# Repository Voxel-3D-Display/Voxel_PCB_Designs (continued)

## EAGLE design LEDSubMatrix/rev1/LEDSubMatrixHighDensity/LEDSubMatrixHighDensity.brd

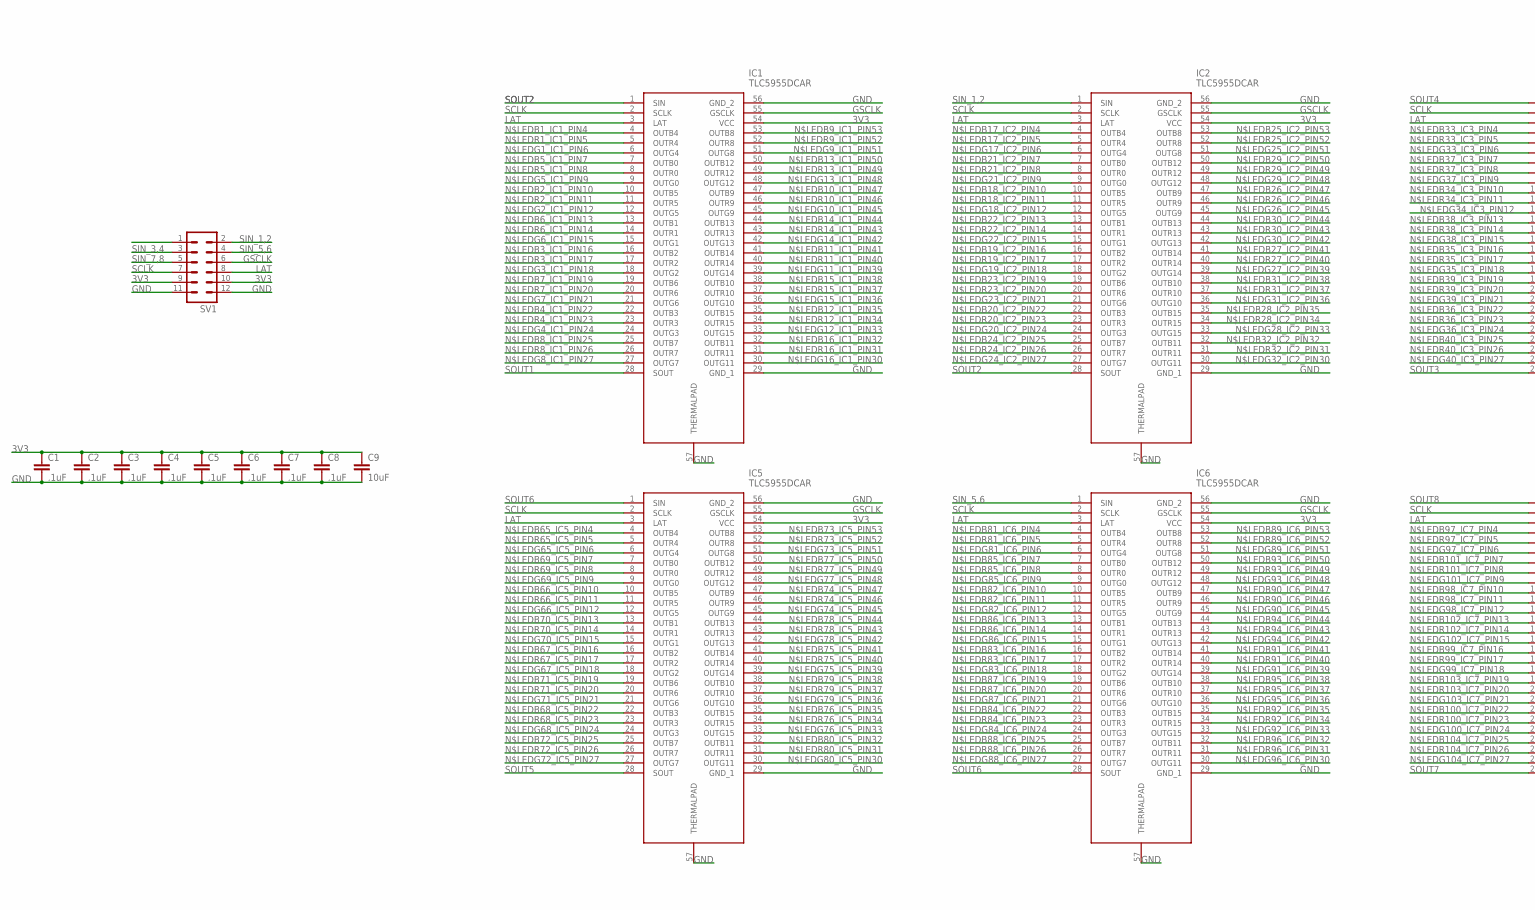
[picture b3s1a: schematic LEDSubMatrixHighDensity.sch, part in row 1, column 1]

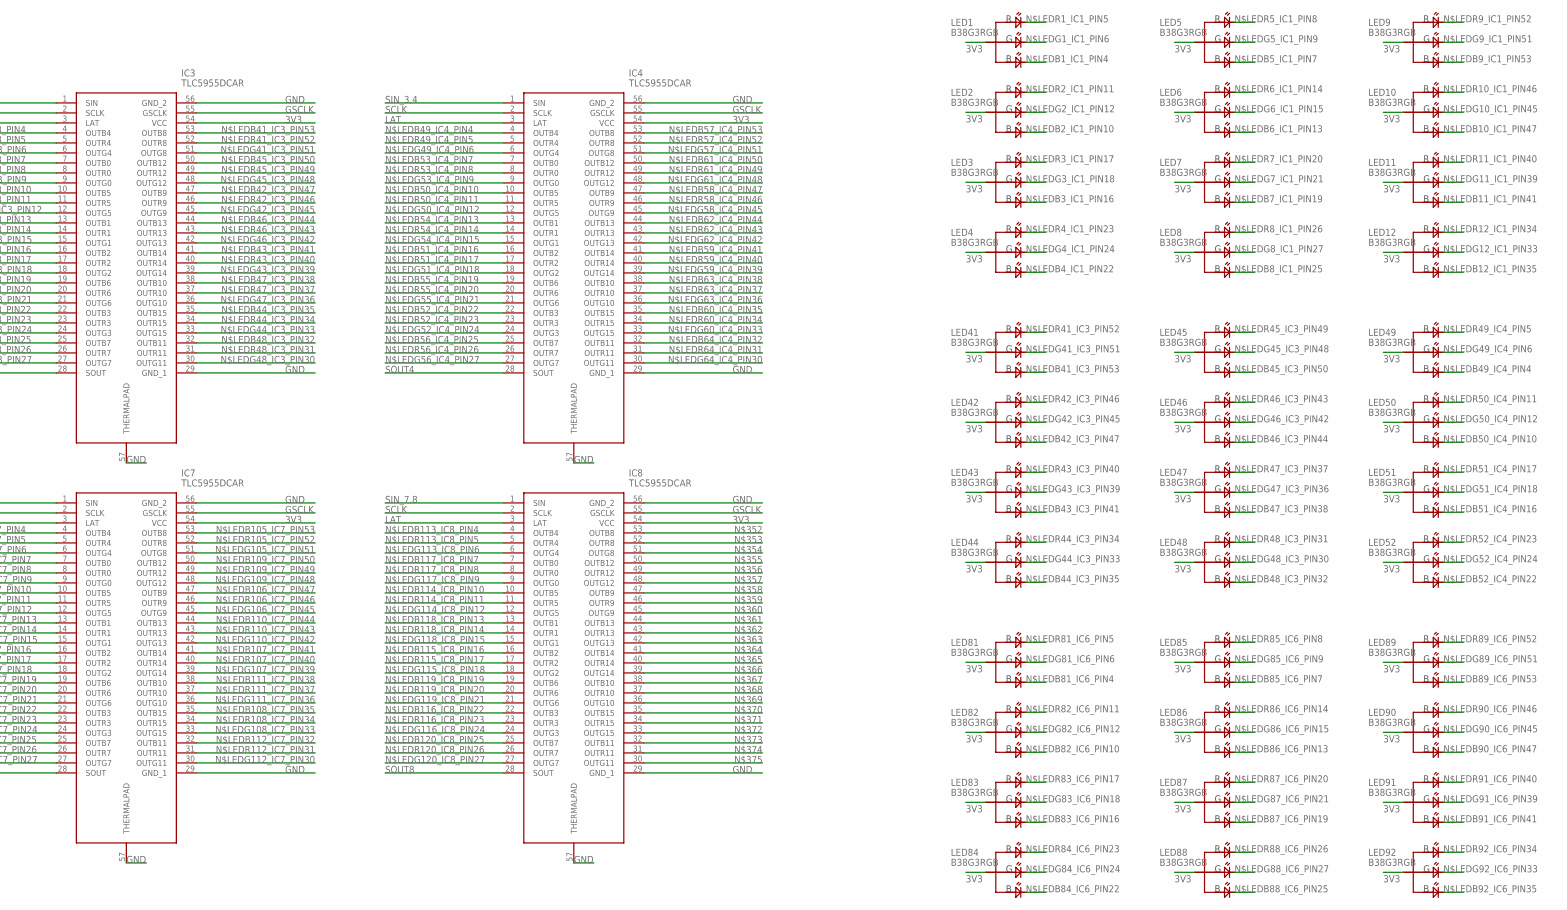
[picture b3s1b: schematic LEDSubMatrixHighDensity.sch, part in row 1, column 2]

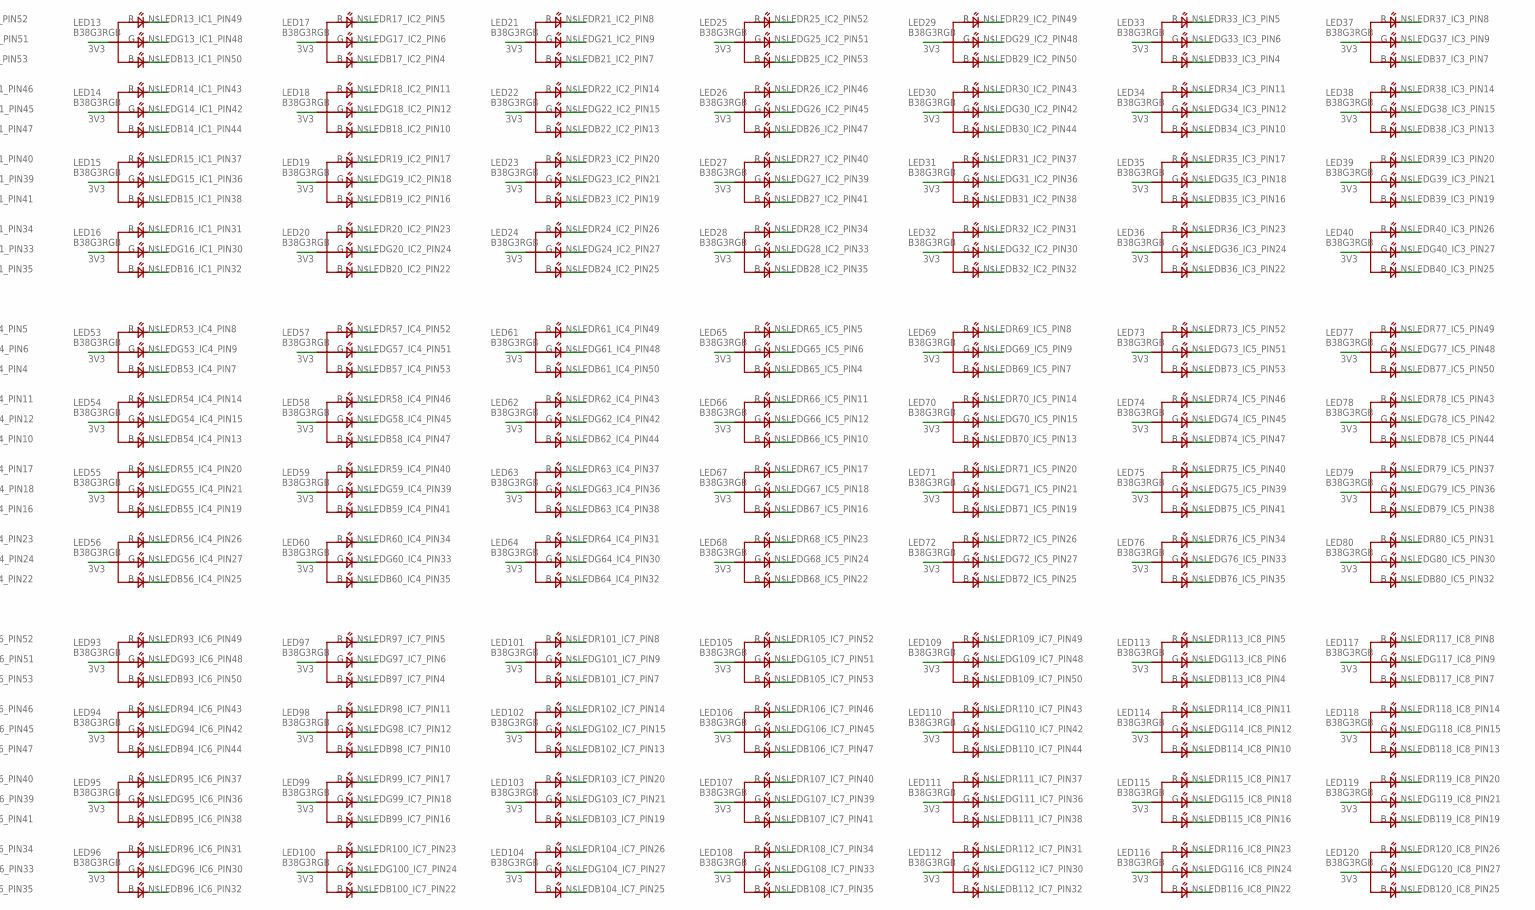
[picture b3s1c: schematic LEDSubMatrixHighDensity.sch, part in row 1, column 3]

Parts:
C1, C2, C3, C4, C5, C6, C7, C8: .1uF; C0603
C9: 10uF; C0805
IC1, IC2, IC3, IC4, IC5, IC6, IC7, IC8: TLC5955DCAR; SOP50P810X120-57N
LED1, LED2, LED3, LED4, LED5, LED6, LED7, LED8, LED9, LED10, LED11, LED12, LED13, LED14, LED15, LED16, LED17, LED18, LED19, LED20, LED21, LED22, LED23, LED24, LED25, LED26, LED27, LED28, LED29, LED30, LED31, LED32, LED33, LED34, LED35, LED36, LED37, LED38, LED39, LED40, LED41, LED42, LED43, LED44, LED45, LED46, LED47, LED48, LED49, LED50, LED51, LED52, LED53, LED54, LED55, LED56, LED57, LED58, LED59, LED60, LED61, LED62, LED63, LED64, LED65, LED66, LED67, LED68, LED69, LED70, LED71, LED72, LED73, LED74, LED75, LED76, LED77, LED78, LED79, LED80, LED81, LED82, LED83, LED84, LED85, LED86, LED87, LED88, LED89, LED90, LED91, LED92, LED93, LED94, LED95, LED96, LED97, LED98, LED99, LED100, LED101, LED102, LED103, LED104, LED105, LED106, LED107, LED108, LED109, LED110, LED111, LED112, LED113, LED114, LED115, LED116, LED117, LED118, LED119, LED120: B38G3RGB
SV1: MA06-2

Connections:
3V3: C1.1, C2.1, C3.1, C4.1, C5.1, C6.1, C7.1, C8.1, C9.1, IC1.54 (VCC), IC2.54 (VCC), IC3.54 (VCC), IC4.54 (VCC), IC5.54 (VCC), IC6.54 (VCC), IC7.54 (VCC), IC8.54 (VCC), LED1.3 (COM), LED2.3 (COM), LED3.3 (COM), LED4.3 (COM), LED5.3 (COM), LED6.3 (COM), LED7.3 (COM), LED8.3 (COM), LED9.3 (COM), LED10.3 (COM), LED11.3 (COM), LED12.3 (COM), LED13.3 (COM), LED14.3 (COM), LED15.3 (COM), LED16.3 (COM), LED17.3 (COM), LED18.3 (COM), LED19.3 (COM), LED20.3 (COM), LED21.3 (COM), LED22.3 (COM), LED23.3 (COM), LED24.3 (COM), LED25.3 (COM), LED26.3 (COM), LED27.3 (COM), LED28.3 (COM), LED29.3 (COM), LED30.3 (COM), LED31.3 (COM), LED32.3 (COM), LED33.3 (COM), LED34.3 (COM), LED35.3 (COM), LED36.3 (COM), LED37.3 (COM), LED38.3 (COM), LED39.3 (COM), LED40.3 (COM), LED41.3 (COM), LED42.3 (COM), LED43.3 (COM), LED44.3 (COM), LED45.3 (COM), LED46.3 (COM), LED47.3 (COM), LED48.3 (COM), LED49.3 (COM), LED50.3 (COM), LED51.3 (COM), LED52.3 (COM), LED53.3 (COM), LED54.3 (COM), LED55.3 (COM), LED56.3 (COM), LED57.3 (COM), LED58.3 (COM), LED59.3 (COM), LED60.3 (COM), LED61.3 (COM), LED62.3 (COM), LED63.3 (COM), LED64.3 (COM), LED65.3 (COM), LED66.3 (COM), LED67.3 (COM), LED68.3 (COM), LED69.3 (COM), LED70.3 (COM), LED71.3 (COM), LED72.3 (COM), LED73.3 (COM), LED74.3 (COM), LED75.3 (COM), LED76.3 (COM), LED77.3 (COM), LED78.3 (COM), LED79.3 (COM), LED80.3 (COM), LED81.3 (COM), LED82.3 (COM), LED83.3 (COM), LED84.3 (COM), LED85.3 (COM), LED86.3 (COM), LED87.3 (COM), LED88.3 (COM), LED89.3 (COM), LED90.3 (COM), LED91.3 (COM), LED92.3 (COM), LED93.3 (COM), LED94.3 (COM), LED95.3 (COM), LED96.3 (COM), LED97.3 (COM), LED98.3 (COM), LED99.3 (COM), LED100.3 (COM), LED101.3 (COM), LED102.3 (COM), LED103.3 (COM), LED104.3 (COM), LED105.3 (COM), LED106.3 (COM), LED107.3 (COM), LED108.3 (COM), LED109.3 (COM), LED110.3 (COM), LED111.3 (COM), LED112.3 (COM), LED113.3 (COM), LED114.3 (COM), LED115.3 (COM), LED116.3 (COM), LED117.3 (COM), LED118.3 (COM), LED119.3 (COM), LED120.3 (COM), SV1.9, SV1.10
GND: C1.2, C2.2, C3.2, C4.2, C5.2, C6.2, C7.2, C8.2, C9.2, IC1.29 (GND_1), IC1.56 (GND_2), IC1.57 (THERMALPAD), IC2.29 (GND_1), IC2.56 (GND_2), IC2.57 (THERMALPAD), IC3.29 (GND_1), IC3.56 (GND_2), IC3.57 (THERMALPAD), IC4.29 (GND_1), IC4.56 (GND_2), IC4.57 (THERMALPAD), IC5.29 (GND_1), IC5.56 (GND_2), IC5.57 (THERMALPAD), IC6.29 (GND_1), IC6.56 (GND_2), IC6.57 (THERMALPAD), IC7.29 (GND_1), IC7.56 (GND_2), IC7.57 (THERMALPAD), IC8.29 (GND_1), IC8.56 (GND_2), IC8.57 (THERMALPAD), SV1.11, SV1.12
GSCLK: IC1.55 (GSCLK), IC2.55 (GSCLK), IC3.55 (GSCLK), IC4.55 (GSCLK), IC5.55 (GSCLK), IC6.55 (GSCLK), IC7.55 (GSCLK), IC8.55 (GSCLK), SV1.6
LAT: IC1.3 (LAT), IC2.3 (LAT), IC3.3 (LAT), IC4.3 (LAT), IC5.3 (LAT), IC6.3 (LAT), IC7.3 (LAT), IC8.3 (LAT), SV1.8
N$LEDB1_IC1_PIN4: IC1.4 (OUTB4), LED1.2 (BLUE)
N$LEDB2_IC1_PIN10: IC1.10 (OUTB5), LED2.2 (BLUE)
N$LEDB3_IC1_PIN16: IC1.16 (OUTB2), LED3.2 (BLUE)
N$LEDB4_IC1_PIN22: IC1.22 (OUTB3), LED4.2 (BLUE)
N$LEDB5_IC1_PIN7: IC1.7 (OUTB0), LED5.2 (BLUE)
N$LEDB6_IC1_PIN13: IC1.13 (OUTB1), LED6.2 (BLUE)
N$LEDB7_IC1_PIN19: IC1.19 (OUTB6), LED7.2 (BLUE)
N$LEDB8_IC1_PIN25: IC1.25 (OUTB7), LED8.2 (BLUE)
N$LEDB9_IC1_PIN53: IC1.53 (OUTB8), LED9.2 (BLUE)
N$LEDB10_IC1_PIN47: IC1.47 (OUTB9), LED10.2 (BLUE)
N$LEDB11_IC1_PIN41: IC1.41 (OUTB14), LED11.2 (BLUE)
N$LEDB12_IC1_PIN35: IC1.35 (OUTB15), LED12.2 (BLUE)
N$LEDB13_IC1_PIN50: IC1.50 (OUTB12), LED13.2 (BLUE)
N$LEDB14_IC1_PIN44: IC1.44 (OUTB13), LED14.2 (BLUE)
N$LEDB15_IC1_PIN38: IC1.38 (OUTB10), LED15.2 (BLUE)
N$LEDB16_IC1_PIN32: IC1.32 (OUTB11), LED16.2 (BLUE)
N$LEDB17_IC2_PIN4: IC2.4 (OUTB4), LED17.2 (BLUE)
N$LEDB18_IC2_PIN10: IC2.10 (OUTB5), LED18.2 (BLUE)
N$LEDB19_IC2_PIN16: IC2.16 (OUTB2), LED19.2 (BLUE)
N$LEDB20_IC2_PIN22: IC2.22 (OUTB3), LED20.2 (BLUE)
N$LEDB21_IC2_PIN7: IC2.7 (OUTB0), LED21.2 (BLUE)
N$LEDB22_IC2_PIN13: IC2.13 (OUTB1), LED22.2 (BLUE)
N$LEDB23_IC2_PIN19: IC2.19 (OUTB6), LED23.2 (BLUE)
N$LEDB24_IC2_PIN25: IC2.25 (OUTB7), LED24.2 (BLUE)
N$LEDB25_IC2_PIN53: IC2.53 (OUTB8), LED25.2 (BLUE)
N$LEDB26_IC2_PIN47: IC2.47 (OUTB9), LED26.2 (BLUE)
N$LEDB27_IC2_PIN41: IC2.41 (OUTB14), LED27.2 (BLUE)
N$LEDB28_IC2_PIN35: IC2.35 (OUTB15), LED28.2 (BLUE)
N$LEDB29_IC2_PIN50: IC2.50 (OUTB12), LED29.2 (BLUE)
N$LEDB30_IC2_PIN44: IC2.44 (OUTB13), LED30.2 (BLUE)
N$LEDB31_IC2_PIN38: IC2.38 (OUTB10), LED31.2 (BLUE)
N$LEDB32_IC2_PIN32: IC2.32 (OUTB11), LED32.2 (BLUE)
N$LEDB33_IC3_PIN4: IC3.4 (OUTB4), LED33.2 (BLUE)
N$LEDB34_IC3_PIN10: IC3.10 (OUTB5), LED34.2 (BLUE)
N$LEDB35_IC3_PIN16: IC3.16 (OUTB2), LED35.2 (BLUE)
N$LEDB36_IC3_PIN22: IC3.22 (OUTB3), LED36.2 (BLUE)
N$LEDB37_IC3_PIN7: IC3.7 (OUTB0), LED37.2 (BLUE)
N$LEDB38_IC3_PIN13: IC3.13 (OUTB1), LED38.2 (BLUE)
N$LEDB39_IC3_PIN19: IC3.19 (OUTB6), LED39.2 (BLUE)
N$LEDB40_IC3_PIN25: IC3.25 (OUTB7), LED40.2 (BLUE)
N$LEDB41_IC3_PIN53: IC3.53 (OUTB8), LED41.2 (BLUE)
N$LEDB42_IC3_PIN47: IC3.47 (OUTB9), LED42.2 (BLUE)
N$LEDB43_IC3_PIN41: IC3.41 (OUTB14), LED43.2 (BLUE)
N$LEDB44_IC3_PIN35: IC3.35 (OUTB15), LED44.2 (BLUE)
N$LEDB45_IC3_PIN50: IC3.50 (OUTB12), LED45.2 (BLUE)
N$LEDB46_IC3_PIN44: IC3.44 (OUTB13), LED46.2 (BLUE)
N$LEDB47_IC3_PIN38: IC3.38 (OUTB10), LED47.2 (BLUE)
N$LEDB48_IC3_PIN32: IC3.32 (OUTB11), LED48.2 (BLUE)
N$LEDB49_IC4_PIN4: IC4.4 (OUTB4), LED49.2 (BLUE)
N$LEDB50_IC4_PIN10: IC4.10 (OUTB5), LED50.2 (BLUE)
N$LEDB51_IC4_PIN16: IC4.16 (OUTB2), LED51.2 (BLUE)
N$LEDB52_IC4_PIN22: IC4.22 (OUTB3), LED52.2 (BLUE)
N$LEDB53_IC4_PIN7: IC4.7 (OUTB0), LED53.2 (BLUE)
N$LEDB54_IC4_PIN13: IC4.13 (OUTB1), LED54.2 (BLUE)
N$LEDB55_IC4_PIN19: IC4.19 (OUTB6), LED55.2 (BLUE)
N$LEDB56_IC4_PIN25: IC4.25 (OUTB7), LED56.2 (BLUE)
N$LEDB57_IC4_PIN53: IC4.53 (OUTB8), LED57.2 (BLUE)
N$LEDB58_IC4_PIN47: IC4.47 (OUTB9), LED58.2 (BLUE)
N$LEDB59_IC4_PIN41: IC4.41 (OUTB14), LED59.2 (BLUE)
N$LEDB60_IC4_PIN35: IC4.35 (OUTB15), LED60.2 (BLUE)
N$LEDB61_IC4_PIN50: IC4.50 (OUTB12), LED61.2 (BLUE)
N$LEDB62_IC4_PIN44: IC4.44 (OUTB13), LED62.2 (BLUE)
N$LEDB63_IC4_PIN38: IC4.38 (OUTB10), LED63.2 (BLUE)
N$LEDB64_IC4_PIN32: IC4.32 (OUTB11), LED64.2 (BLUE)
N$LEDB65_IC5_PIN4: IC5.4 (OUTB4), LED65.2 (BLUE)
N$LEDB66_IC5_PIN10: IC5.10 (OUTB5), LED66.2 (BLUE)
N$LEDB67_IC5_PIN16: IC5.16 (OUTB2), LED67.2 (BLUE)
N$LEDB68_IC5_PIN22: IC5.22 (OUTB3), LED68.2 (BLUE)
N$LEDB69_IC5_PIN7: IC5.7 (OUTB0), LED69.2 (BLUE)
N$LEDB70_IC5_PIN13: IC5.13 (OUTB1), LED70.2 (BLUE)
N$LEDB71_IC5_PIN19: IC5.19 (OUTB6), LED71.2 (BLUE)
N$LEDB72_IC5_PIN25: IC5.25 (OUTB7), LED72.2 (BLUE)
N$LEDB73_IC5_PIN53: IC5.53 (OUTB8), LED73.2 (BLUE)
N$LEDB74_IC5_PIN47: IC5.47 (OUTB9), LED74.2 (BLUE)
N$LEDB75_IC5_PIN41: IC5.41 (OUTB14), LED75.2 (BLUE)
N$LEDB76_IC5_PIN35: IC5.35 (OUTB15), LED76.2 (BLUE)
N$LEDB77_IC5_PIN50: IC5.50 (OUTB12), LED77.2 (BLUE)
N$LEDB78_IC5_PIN44: IC5.44 (OUTB13), LED78.2 (BLUE)
N$LEDB79_IC5_PIN38: IC5.38 (OUTB10), LED79.2 (BLUE)
N$LEDB80_IC5_PIN32: IC5.32 (OUTB11), LED80.2 (BLUE)
N$LEDB81_IC6_PIN4: IC6.4 (OUTB4), LED81.2 (BLUE)
N$LEDB82_IC6_PIN10: IC6.10 (OUTB5), LED82.2 (BLUE)
N$LEDB83_IC6_PIN16: IC6.16 (OUTB2), LED83.2 (BLUE)
N$LEDB84_IC6_PIN22: IC6.22 (OUTB3), LED84.2 (BLUE)
N$LEDB85_IC6_PIN7: IC6.7 (OUTB0), LED85.2 (BLUE)
N$LEDB86_IC6_PIN13: IC6.13 (OUTB1), LED86.2 (BLUE)
N$LEDB87_IC6_PIN19: IC6.19 (OUTB6), LED87.2 (BLUE)
N$LEDB88_IC6_PIN25: IC6.25 (OUTB7), LED88.2 (BLUE)
N$LEDB89_IC6_PIN53: IC6.53 (OUTB8), LED89.2 (BLUE)
N$LEDB90_IC6_PIN47: IC6.47 (OUTB9), LED90.2 (BLUE)
N$LEDB91_IC6_PIN41: IC6.41 (OUTB14), LED91.2 (BLUE)
N$LEDB92_IC6_PIN35: IC6.35 (OUTB15), LED92.2 (BLUE)
N$LEDB93_IC6_PIN50: IC6.50 (OUTB12), LED93.2 (BLUE)
N$LEDB94_IC6_PIN44: IC6.44 (OUTB13), LED94.2 (BLUE)
N$LEDB95_IC6_PIN38: IC6.38 (OUTB10), LED95.2 (BLUE)
N$LEDB96_IC6_PIN32: IC6.32 (OUTB11), LED96.2 (BLUE)
N$LEDB97_IC7_PIN4: IC7.4 (OUTB4), LED97.2 (BLUE)
N$LEDB98_IC7_PIN10: IC7.10 (OUTB5), LED98.2 (BLUE)
N$LEDB99_IC7_PIN16: IC7.16 (OUTB2), LED99.2 (BLUE)
N$LEDB100_IC7_PIN22: IC7.22 (OUTB3), LED100.2 (BLUE)
N$LEDB101_IC7_PIN7: IC7.7 (OUTB0), LED101.2 (BLUE)
N$LEDB102_IC7_PIN13: IC7.13 (OUTB1), LED102.2 (BLUE)
N$LEDB103_IC7_PIN19: IC7.19 (OUTB6), LED103.2 (BLUE)
N$LEDB104_IC7_PIN25: IC7.25 (OUTB7), LED104.2 (BLUE)
N$LEDB105_IC7_PIN53: IC7.53 (OUTB8), LED105.2 (BLUE)
N$LEDB106_IC7_PIN47: IC7.47 (OUTB9), LED106.2 (BLUE)
N$LEDB107_IC7_PIN41: IC7.41 (OUTB14), LED107.2 (BLUE)
N$LEDB108_IC7_PIN35: IC7.35 (OUTB15), LED108.2 (BLUE)
N$LEDB109_IC7_PIN50: IC7.50 (OUTB12), LED109.2 (BLUE)
N$LEDB110_IC7_PIN44: IC7.44 (OUTB13), LED110.2 (BLUE)
N$LEDB111_IC7_PIN38: IC7.38 (OUTB10), LED111.2 (BLUE)
N$LEDB112_IC7_PIN32: IC7.32 (OUTB11), LED112.2 (BLUE)
N$LEDB113_IC8_PIN4: IC8.4 (OUTB4), LED113.2 (BLUE)
N$LEDB114_IC8_PIN10: IC8.10 (OUTB5), LED114.2 (BLUE)
N$LEDB115_IC8_PIN16: IC8.16 (OUTB2), LED115.2 (BLUE)
N$LEDB116_IC8_PIN22: IC8.22 (OUTB3), LED116.2 (BLUE)
N$LEDB117_IC8_PIN7: IC8.7 (OUTB0), LED117.2 (BLUE)
N$LEDB118_IC8_PIN13: IC8.13 (OUTB1), LED118.2 (BLUE)
N$LEDB119_IC8_PIN19: IC8.19 (OUTB6), LED119.2 (BLUE)
N$LEDB120_IC8_PIN25: IC8.25 (OUTB7), LED120.2 (BLUE)
N$LEDG1_IC1_PIN6: IC1.6 (OUTG4), LED1.1 (GREEN)
N$LEDG2_IC1_PIN12: IC1.12 (OUTG5), LED2.1 (GREEN)
N$LEDG3_IC1_PIN18: IC1.18 (OUTG2), LED3.1 (GREEN)
N$LEDG4_IC1_PIN24: IC1.24 (OUTG3), LED4.1 (GREEN)
N$LEDG5_IC1_PIN9: IC1.9 (OUTG0), LED5.1 (GREEN)
N$LEDG6_IC1_PIN15: IC1.15 (OUTG1), LED6.1 (GREEN)
N$LEDG7_IC1_PIN21: IC1.21 (OUTG6), LED7.1 (GREEN)
N$LEDG8_IC1_PIN27: IC1.27 (OUTG7), LED8.1 (GREEN)
N$LEDG9_IC1_PIN51: IC1.51 (OUTG8), LED9.1 (GREEN)
N$LEDG10_IC1_PIN45: IC1.45 (OUTG9), LED10.1 (GREEN)
N$LEDG11_IC1_PIN39: IC1.39 (OUTG14), LED11.1 (GREEN)
N$LEDG12_IC1_PIN33: IC1.33 (OUTG15), LED12.1 (GREEN)
N$LEDG13_IC1_PIN48: IC1.48 (OUTG12), LED13.1 (GREEN)
N$LEDG14_IC1_PIN42: IC1.42 (OUTG13), LED14.1 (GREEN)
N$LEDG15_IC1_PIN36: IC1.36 (OUTG10), LED15.1 (GREEN)
N$LEDG16_IC1_PIN30: IC1.30 (OUTG11), LED16.1 (GREEN)
N$LEDG17_IC2_PIN6: IC2.6 (OUTG4), LED17.1 (GREEN)
N$LEDG18_IC2_PIN12: IC2.12 (OUTG5), LED18.1 (GREEN)
N$LEDG19_IC2_PIN18: IC2.18 (OUTG2), LED19.1 (GREEN)
N$LEDG20_IC2_PIN24: IC2.24 (OUTG3), LED20.1 (GREEN)
N$LEDG21_IC2_PIN9: IC2.9 (OUTG0), LED21.1 (GREEN)
N$LEDG22_IC2_PIN15: IC2.15 (OUTG1), LED22.1 (GREEN)
N$LEDG23_IC2_PIN21: IC2.21 (OUTG6), LED23.1 (GREEN)
N$LEDG24_IC2_PIN27: IC2.27 (OUTG7), LED24.1 (GREEN)
N$LEDG25_IC2_PIN51: IC2.51 (OUTG8), LED25.1 (GREEN)
N$LEDG26_IC2_PIN45: IC2.45 (OUTG9), LED26.1 (GREEN)
N$LEDG27_IC2_PIN39: IC2.39 (OUTG14), LED27.1 (GREEN)
N$LEDG28_IC2_PIN33: IC2.33 (OUTG15), LED28.1 (GREEN)
N$LEDG29_IC2_PIN48: IC2.48 (OUTG12), LED29.1 (GREEN)
N$LEDG30_IC2_PIN42: IC2.42 (OUTG13), LED30.1 (GREEN)
N$LEDG31_IC2_PIN36: IC2.36 (OUTG10), LED31.1 (GREEN)
N$LEDG32_IC2_PIN30: IC2.30 (OUTG11), LED32.1 (GREEN)
N$LEDG33_IC3_PIN6: IC3.6 (OUTG4), LED33.1 (GREEN)
N$LEDG34_IC3_PIN12: IC3.12 (OUTG5), LED34.1 (GREEN)
N$LEDG35_IC3_PIN18: IC3.18 (OUTG2), LED35.1 (GREEN)
N$LEDG36_IC3_PIN24: IC3.24 (OUTG3), LED36.1 (GREEN)
N$LEDG37_IC3_PIN9: IC3.9 (OUTG0), LED37.1 (GREEN)
N$LEDG38_IC3_PIN15: IC3.15 (OUTG1), LED38.1 (GREEN)
N$LEDG39_IC3_PIN21: IC3.21 (OUTG6), LED39.1 (GREEN)
N$LEDG40_IC3_PIN27: IC3.27 (OUTG7), LED40.1 (GREEN)
N$LEDG41_IC3_PIN51: IC3.51 (OUTG8), LED41.1 (GREEN)
N$LEDG42_IC3_PIN45: IC3.45 (OUTG9), LED42.1 (GREEN)
N$LEDG43_IC3_PIN39: IC3.39 (OUTG14), LED43.1 (GREEN)
N$LEDG44_IC3_PIN33: IC3.33 (OUTG15), LED44.1 (GREEN)
N$LEDG45_IC3_PIN48: IC3.48 (OUTG12), LED45.1 (GREEN)
N$LEDG46_IC3_PIN42: IC3.42 (OUTG13), LED46.1 (GREEN)
N$LEDG47_IC3_PIN36: IC3.36 (OUTG10), LED47.1 (GREEN)
N$LEDG48_IC3_PIN30: IC3.30 (OUTG11), LED48.1 (GREEN)
N$LEDG49_IC4_PIN6: IC4.6 (OUTG4), LED49.1 (GREEN)
N$LEDG50_IC4_PIN12: IC4.12 (OUTG5), LED50.1 (GREEN)
N$LEDG51_IC4_PIN18: IC4.18 (OUTG2), LED51.1 (GREEN)
N$LEDG52_IC4_PIN24: IC4.24 (OUTG3), LED52.1 (GREEN)
N$LEDG53_IC4_PIN9: IC4.9 (OUTG0), LED53.1 (GREEN)
N$LEDG54_IC4_PIN15: IC4.15 (OUTG1), LED54.1 (GREEN)
N$LEDG55_IC4_PIN21: IC4.21 (OUTG6), LED55.1 (GREEN)
N$LEDG56_IC4_PIN27: IC4.27 (OUTG7), LED56.1 (GREEN)
N$LEDG57_IC4_PIN51: IC4.51 (OUTG8), LED57.1 (GREEN)
N$LEDG58_IC4_PIN45: IC4.45 (OUTG9), LED58.1 (GREEN)
N$LEDG59_IC4_PIN39: IC4.39 (OUTG14), LED59.1 (GREEN)
N$LEDG60_IC4_PIN33: IC4.33 (OUTG15), LED60.1 (GREEN)
N$LEDG61_IC4_PIN48: IC4.48 (OUTG12), LED61.1 (GREEN)
N$LEDG62_IC4_PIN42: IC4.42 (OUTG13), LED62.1 (GREEN)
N$LEDG63_IC4_PIN36: IC4.36 (OUTG10), LED63.1 (GREEN)
N$LEDG64_IC4_PIN30: IC4.30 (OUTG11), LED64.1 (GREEN)
N$LEDG65_IC5_PIN6: IC5.6 (OUTG4), LED65.1 (GREEN)
N$LEDG66_IC5_PIN12: IC5.12 (OUTG5), LED66.1 (GREEN)
N$LEDG67_IC5_PIN18: IC5.18 (OUTG2), LED67.1 (GREEN)
N$LEDG68_IC5_PIN24: IC5.24 (OUTG3), LED68.1 (GREEN)
N$LEDG69_IC5_PIN9: IC5.9 (OUTG0), LED69.1 (GREEN)
N$LEDG70_IC5_PIN15: IC5.15 (OUTG1), LED70.1 (GREEN)
N$LEDG71_IC5_PIN21: IC5.21 (OUTG6), LED71.1 (GREEN)
N$LEDG72_IC5_PIN27: IC5.27 (OUTG7), LED72.1 (GREEN)
N$LEDG73_IC5_PIN51: IC5.51 (OUTG8), LED73.1 (GREEN)
N$LEDG74_IC5_PIN45: IC5.45 (OUTG9), LED74.1 (GREEN)
N$LEDG75_IC5_PIN39: IC5.39 (OUTG14), LED75.1 (GREEN)
N$LEDG76_IC5_PIN33: IC5.33 (OUTG15), LED76.1 (GREEN)
N$LEDG77_IC5_PIN48: IC5.48 (OUTG12), LED77.1 (GREEN)
N$LEDG78_IC5_PIN42: IC5.42 (OUTG13), LED78.1 (GREEN)
N$LEDG79_IC5_PIN36: IC5.36 (OUTG10), LED79.1 (GREEN)
N$LEDG80_IC5_PIN30: IC5.30 (OUTG11), LED80.1 (GREEN)
N$LEDG81_IC6_PIN6: IC6.6 (OUTG4), LED81.1 (GREEN)
N$LEDG82_IC6_PIN12: IC6.12 (OUTG5), LED82.1 (GREEN)
N$LEDG83_IC6_PIN18: IC6.18 (OUTG2), LED83.1 (GREEN)
N$LEDG84_IC6_PIN24: IC6.24 (OUTG3), LED84.1 (GREEN)
N$LEDG85_IC6_PIN9: IC6.9 (OUTG0), LED85.1 (GREEN)
N$LEDG86_IC6_PIN15: IC6.15 (OUTG1), LED86.1 (GREEN)
N$LEDG87_IC6_PIN21: IC6.21 (OUTG6), LED87.1 (GREEN)
N$LEDG88_IC6_PIN27: IC6.27 (OUTG7), LED88.1 (GREEN)
N$LEDG89_IC6_PIN51: IC6.51 (OUTG8), LED89.1 (GREEN)
N$LEDG90_IC6_PIN45: IC6.45 (OUTG9), LED90.1 (GREEN)
N$LEDG91_IC6_PIN39: IC6.39 (OUTG14), LED91.1 (GREEN)
N$LEDG92_IC6_PIN33: IC6.33 (OUTG15), LED92.1 (GREEN)
N$LEDG93_IC6_PIN48: IC6.48 (OUTG12), LED93.1 (GREEN)
N$LEDG94_IC6_PIN42: IC6.42 (OUTG13), LED94.1 (GREEN)
N$LEDG95_IC6_PIN36: IC6.36 (OUTG10), LED95.1 (GREEN)
N$LEDG96_IC6_PIN30: IC6.30 (OUTG11), LED96.1 (GREEN)
N$LEDG97_IC7_PIN6: IC7.6 (OUTG4), LED97.1 (GREEN)
N$LEDG98_IC7_PIN12: IC7.12 (OUTG5), LED98.1 (GREEN)
N$LEDG99_IC7_PIN18: IC7.18 (OUTG2), LED99.1 (GREEN)
N$LEDG100_IC7_PIN24: IC7.24 (OUTG3), LED100.1 (GREEN)
N$LEDG101_IC7_PIN9: IC7.9 (OUTG0), LED101.1 (GREEN)
N$LEDG102_IC7_PIN15: IC7.15 (OUTG1), LED102.1 (GREEN)
N$LEDG103_IC7_PIN21: IC7.21 (OUTG6), LED103.1 (GREEN)
N$LEDG104_IC7_PIN27: IC7.27 (OUTG7), LED104.1 (GREEN)
N$LEDG105_IC7_PIN51: IC7.51 (OUTG8), LED105.1 (GREEN)
N$LEDG106_IC7_PIN45: IC7.45 (OUTG9), LED106.1 (GREEN)
N$LEDG107_IC7_PIN39: IC7.39 (OUTG14), LED107.1 (GREEN)
N$LEDG108_IC7_PIN33: IC7.33 (OUTG15), LED108.1 (GREEN)
N$LEDG109_IC7_PIN48: IC7.48 (OUTG12), LED109.1 (GREEN)
N$LEDG110_IC7_PIN42: IC7.42 (OUTG13), LED110.1 (GREEN)
N$LEDG111_IC7_PIN36: IC7.36 (OUTG10), LED111.1 (GREEN)
N$LEDG112_IC7_PIN30: IC7.30 (OUTG11), LED112.1 (GREEN)
N$LEDG113_IC8_PIN6: IC8.6 (OUTG4), LED113.1 (GREEN)
N$LEDG114_IC8_PIN12: IC8.12 (OUTG5), LED114.1 (GREEN)
N$LEDG115_IC8_PIN18: IC8.18 (OUTG2), LED115.1 (GREEN)
N$LEDG116_IC8_PIN24: IC8.24 (OUTG3), LED116.1 (GREEN)
N$LEDG117_IC8_PIN9: IC8.9 (OUTG0), LED117.1 (GREEN)
N$LEDG118_IC8_PIN15: IC8.15 (OUTG1), LED118.1 (GREEN)
N$LEDG119_IC8_PIN21: IC8.21 (OUTG6), LED119.1 (GREEN)
N$LEDG120_IC8_PIN27: IC8.27 (OUTG7), LED120.1 (GREEN)
N$LEDR1_IC1_PIN5: IC1.5 (OUTR4), LED1.4 (RED)
N$LEDR2_IC1_PIN11: IC1.11 (OUTR5), LED2.4 (RED)
N$LEDR3_IC1_PIN17: IC1.17 (OUTR2), LED3.4 (RED)
N$LEDR4_IC1_PIN23: IC1.23 (OUTR3), LED4.4 (RED)
N$LEDR5_IC1_PIN8: IC1.8 (OUTR0), LED5.4 (RED)
N$LEDR6_IC1_PIN14: IC1.14 (OUTR1), LED6.4 (RED)
N$LEDR7_IC1_PIN20: IC1.20 (OUTR6), LED7.4 (RED)
N$LEDR8_IC1_PIN26: IC1.26 (OUTR7), LED8.4 (RED)
N$LEDR9_IC1_PIN52: IC1.52 (OUTR8), LED9.4 (RED)
N$LEDR10_IC1_PIN46: IC1.46 (OUTR9), LED10.4 (RED)
N$LEDR11_IC1_PIN40: IC1.40 (OUTR14), LED11.4 (RED)
N$LEDR12_IC1_PIN34: IC1.34 (OUTR15), LED12.4 (RED)
N$LEDR13_IC1_PIN49: IC1.49 (OUTR12), LED13.4 (RED)
N$LEDR14_IC1_PIN43: IC1.43 (OUTR13), LED14.4 (RED)
N$LEDR15_IC1_PIN37: IC1.37 (OUTR10), LED15.4 (RED)
N$LEDR16_IC1_PIN31: IC1.31 (OUTR11), LED16.4 (RED)
N$LEDR17_IC2_PIN5: IC2.5 (OUTR4), LED17.4 (RED)
N$LEDR18_IC2_PIN11: IC2.11 (OUTR5), LED18.4 (RED)
N$LEDR19_IC2_PIN17: IC2.17 (OUTR2), LED19.4 (RED)
N$LEDR20_IC2_PIN23: IC2.23 (OUTR3), LED20.4 (RED)
N$LEDR21_IC2_PIN8: IC2.8 (OUTR0), LED21.4 (RED)
N$LEDR22_IC2_PIN14: IC2.14 (OUTR1), LED22.4 (RED)
N$LEDR23_IC2_PIN20: IC2.20 (OUTR6), LED23.4 (RED)
N$LEDR24_IC2_PIN26: IC2.26 (OUTR7), LED24.4 (RED)
N$LEDR25_IC2_PIN52: IC2.52 (OUTR8), LED25.4 (RED)
N$LEDR26_IC2_PIN46: IC2.46 (OUTR9), LED26.4 (RED)
N$LEDR27_IC2_PIN40: IC2.40 (OUTR14), LED27.4 (RED)
N$LEDR28_IC2_PIN34: IC2.34 (OUTR15), LED28.4 (RED)
N$LEDR29_IC2_PIN49: IC2.49 (OUTR12), LED29.4 (RED)
N$LEDR30_IC2_PIN43: IC2.43 (OUTR13), LED30.4 (RED)
N$LEDR31_IC2_PIN37: IC2.37 (OUTR10), LED31.4 (RED)
N$LEDR32_IC2_PIN31: IC2.31 (OUTR11), LED32.4 (RED)
N$LEDR33_IC3_PIN5: IC3.5 (OUTR4), LED33.4 (RED)
N$LEDR34_IC3_PIN11: IC3.11 (OUTR5), LED34.4 (RED)
N$LEDR35_IC3_PIN17: IC3.17 (OUTR2), LED35.4 (RED)
N$LEDR36_IC3_PIN23: IC3.23 (OUTR3), LED36.4 (RED)
N$LEDR37_IC3_PIN8: IC3.8 (OUTR0), LED37.4 (RED)
N$LEDR38_IC3_PIN14: IC3.14 (OUTR1), LED38.4 (RED)
N$LEDR39_IC3_PIN20: IC3.20 (OUTR6), LED39.4 (RED)
N$LEDR40_IC3_PIN26: IC3.26 (OUTR7), LED40.4 (RED)
N$LEDR41_IC3_PIN52: IC3.52 (OUTR8), LED41.4 (RED)
N$LEDR42_IC3_PIN46: IC3.46 (OUTR9), LED42.4 (RED)
N$LEDR43_IC3_PIN40: IC3.40 (OUTR14), LED43.4 (RED)
N$LEDR44_IC3_PIN34: IC3.34 (OUTR15), LED44.4 (RED)
N$LEDR45_IC3_PIN49: IC3.49 (OUTR12), LED45.4 (RED)
N$LEDR46_IC3_PIN43: IC3.43 (OUTR13), LED46.4 (RED)
N$LEDR47_IC3_PIN37: IC3.37 (OUTR10), LED47.4 (RED)
N$LEDR48_IC3_PIN31: IC3.31 (OUTR11), LED48.4 (RED)
N$LEDR49_IC4_PIN5: IC4.5 (OUTR4), LED49.4 (RED)
N$LEDR50_IC4_PIN11: IC4.11 (OUTR5), LED50.4 (RED)
N$LEDR51_IC4_PIN17: IC4.17 (OUTR2), LED51.4 (RED)
N$LEDR52_IC4_PIN23: IC4.23 (OUTR3), LED52.4 (RED)
N$LEDR53_IC4_PIN8: IC4.8 (OUTR0), LED53.4 (RED)
N$LEDR54_IC4_PIN14: IC4.14 (OUTR1), LED54.4 (RED)
N$LEDR55_IC4_PIN20: IC4.20 (OUTR6), LED55.4 (RED)
N$LEDR56_IC4_PIN26: IC4.26 (OUTR7), LED56.4 (RED)
N$LEDR57_IC4_PIN52: IC4.52 (OUTR8), LED57.4 (RED)
N$LEDR58_IC4_PIN46: IC4.46 (OUTR9), LED58.4 (RED)
N$LEDR59_IC4_PIN40: IC4.40 (OUTR14), LED59.4 (RED)
N$LEDR60_IC4_PIN34: IC4.34 (OUTR15), LED60.4 (RED)
N$LEDR61_IC4_PIN49: IC4.49 (OUTR12), LED61.4 (RED)
N$LEDR62_IC4_PIN43: IC4.43 (OUTR13), LED62.4 (RED)
N$LEDR63_IC4_PIN37: IC4.37 (OUTR10), LED63.4 (RED)
N$LEDR64_IC4_PIN31: IC4.31 (OUTR11), LED64.4 (RED)
N$LEDR65_IC5_PIN5: IC5.5 (OUTR4), LED65.4 (RED)
N$LEDR66_IC5_PIN11: IC5.11 (OUTR5), LED66.4 (RED)
N$LEDR67_IC5_PIN17: IC5.17 (OUTR2), LED67.4 (RED)
N$LEDR68_IC5_PIN23: IC5.23 (OUTR3), LED68.4 (RED)
N$LEDR69_IC5_PIN8: IC5.8 (OUTR0), LED69.4 (RED)
N$LEDR70_IC5_PIN14: IC5.14 (OUTR1), LED70.4 (RED)
N$LEDR71_IC5_PIN20: IC5.20 (OUTR6), LED71.4 (RED)
N$LEDR72_IC5_PIN26: IC5.26 (OUTR7), LED72.4 (RED)
N$LEDR73_IC5_PIN52: IC5.52 (OUTR8), LED73.4 (RED)
N$LEDR74_IC5_PIN46: IC5.46 (OUTR9), LED74.4 (RED)
N$LEDR75_IC5_PIN40: IC5.40 (OUTR14), LED75.4 (RED)
N$LEDR76_IC5_PIN34: IC5.34 (OUTR15), LED76.4 (RED)
N$LEDR77_IC5_PIN49: IC5.49 (OUTR12), LED77.4 (RED)
N$LEDR78_IC5_PIN43: IC5.43 (OUTR13), LED78.4 (RED)
N$LEDR79_IC5_PIN37: IC5.37 (OUTR10), LED79.4 (RED)
N$LEDR80_IC5_PIN31: IC5.31 (OUTR11), LED80.4 (RED)
N$LEDR81_IC6_PIN5: IC6.5 (OUTR4), LED81.4 (RED)
N$LEDR82_IC6_PIN11: IC6.11 (OUTR5), LED82.4 (RED)
N$LEDR83_IC6_PIN17: IC6.17 (OUTR2), LED83.4 (RED)
N$LEDR84_IC6_PIN23: IC6.23 (OUTR3), LED84.4 (RED)
N$LEDR85_IC6_PIN8: IC6.8 (OUTR0), LED85.4 (RED)
N$LEDR86_IC6_PIN14: IC6.14 (OUTR1), LED86.4 (RED)
N$LEDR87_IC6_PIN20: IC6.20 (OUTR6), LED87.4 (RED)
N$LEDR88_IC6_PIN26: IC6.26 (OUTR7), LED88.4 (RED)
N$LEDR89_IC6_PIN52: IC6.52 (OUTR8), LED89.4 (RED)
N$LEDR90_IC6_PIN46: IC6.46 (OUTR9), LED90.4 (RED)
N$LEDR91_IC6_PIN40: IC6.40 (OUTR14), LED91.4 (RED)
N$LEDR92_IC6_PIN34: IC6.34 (OUTR15), LED92.4 (RED)
N$LEDR93_IC6_PIN49: IC6.49 (OUTR12), LED93.4 (RED)
N$LEDR94_IC6_PIN43: IC6.43 (OUTR13), LED94.4 (RED)
N$LEDR95_IC6_PIN37: IC6.37 (OUTR10), LED95.4 (RED)
N$LEDR96_IC6_PIN31: IC6.31 (OUTR11), LED96.4 (RED)
N$LEDR97_IC7_PIN5: IC7.5 (OUTR4), LED97.4 (RED)
N$LEDR98_IC7_PIN11: IC7.11 (OUTR5), LED98.4 (RED)
N$LEDR99_IC7_PIN17: IC7.17 (OUTR2), LED99.4 (RED)
N$LEDR100_IC7_PIN23: IC7.23 (OUTR3), LED100.4 (RED)
N$LEDR101_IC7_PIN8: IC7.8 (OUTR0), LED101.4 (RED)
N$LEDR102_IC7_PIN14: IC7.14 (OUTR1), LED102.4 (RED)
N$LEDR103_IC7_PIN20: IC7.20 (OUTR6), LED103.4 (RED)
N$LEDR104_IC7_PIN26: IC7.26 (OUTR7), LED104.4 (RED)
N$LEDR105_IC7_PIN52: IC7.52 (OUTR8), LED105.4 (RED)
N$LEDR106_IC7_PIN46: IC7.46 (OUTR9), LED106.4 (RED)
N$LEDR107_IC7_PIN40: IC7.40 (OUTR14), LED107.4 (RED)
N$LEDR108_IC7_PIN34: IC7.34 (OUTR15), LED108.4 (RED)
N$LEDR109_IC7_PIN49: IC7.49 (OUTR12), LED109.4 (RED)
N$LEDR110_IC7_PIN43: IC7.43 (OUTR13), LED110.4 (RED)
N$LEDR111_IC7_PIN37: IC7.37 (OUTR10), LED111.4 (RED)
N$LEDR112_IC7_PIN31: IC7.31 (OUTR11), LED112.4 (RED)
N$LEDR113_IC8_PIN5: IC8.5 (OUTR4), LED113.4 (RED)
N$LEDR114_IC8_PIN11: IC8.11 (OUTR5), LED114.4 (RED)
N$LEDR115_IC8_PIN17: IC8.17 (OUTR2), LED115.4 (RED)
N$LEDR116_IC8_PIN23: IC8.23 (OUTR3), LED116.4 (RED)
N$LEDR117_IC8_PIN8: IC8.8 (OUTR0), LED117.4 (RED)
N$LEDR118_IC8_PIN14: IC8.14 (OUTR1), LED118.4 (RED)
N$LEDR119_IC8_PIN20: IC8.20 (OUTR6), LED119.4 (RED)
N$LEDR120_IC8_PIN26: IC8.26 (OUTR7), LED120.4 (RED)
SCLK: IC1.2 (SCLK), IC2.2 (SCLK), IC3.2 (SCLK), IC4.2 (SCLK), IC5.2 (SCLK), IC6.2 (SCLK), IC7.2 (SCLK), IC8.2 (SCLK), SV1.7
SIN_1,2: IC2.1 (SIN), SV1.2
SIN_3,4: IC4.1 (SIN), SV1.3
SIN_5,6: IC6.1 (SIN), SV1.4
SIN_7,8: IC8.1 (SIN), SV1.5
SOUT1: IC1.28 (SOUT)
SOUT2: IC1.1 (SIN), IC2.28 (SOUT)
SOUT3: IC3.28 (SOUT)
SOUT4: IC3.1 (SIN), IC4.28 (SOUT)
SOUT5: IC5.28 (SOUT)
SOUT6: IC5.1 (SIN), IC6.28 (SOUT)
SOUT7: IC7.28 (SOUT)
SOUT8: IC7.1 (SIN), IC8.28 (SOUT)

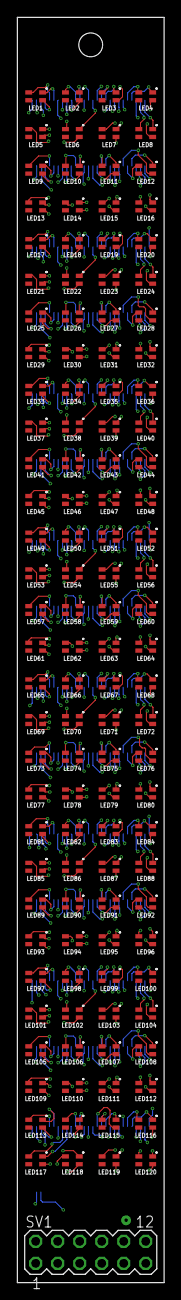
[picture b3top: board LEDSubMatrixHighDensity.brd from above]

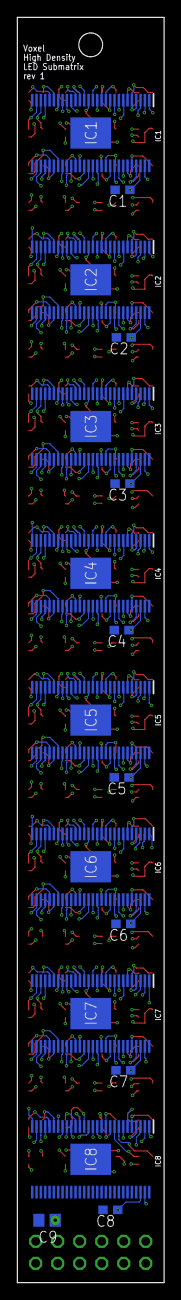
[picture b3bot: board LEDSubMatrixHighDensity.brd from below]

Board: 4 copper layers, 16.9 x 146.0 mm, 138 parts (17 on the bottom side), 373 nets.

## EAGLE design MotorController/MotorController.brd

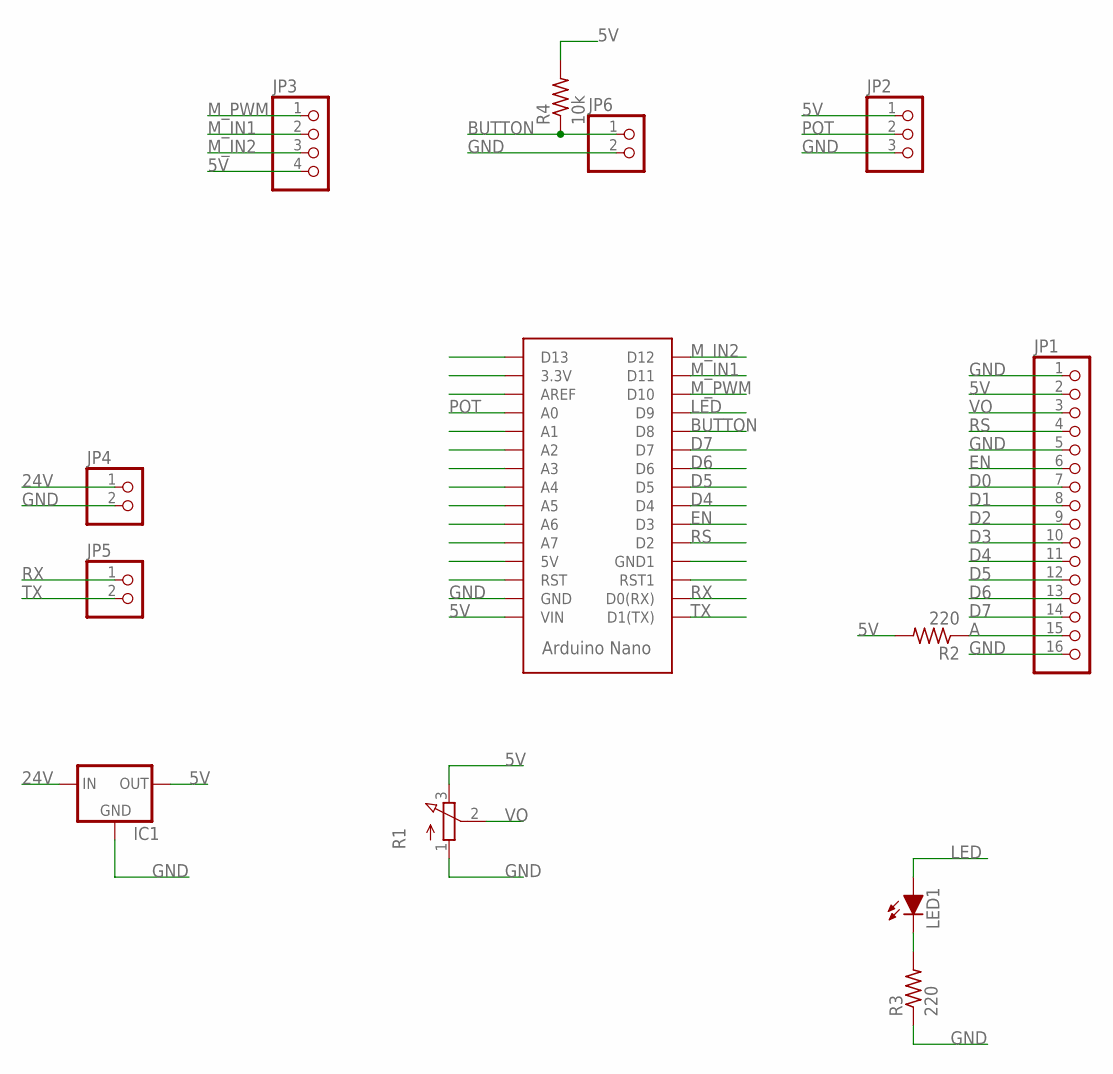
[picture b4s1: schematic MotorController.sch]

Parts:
IC1: REG_5V_L7805_HOR; TO-220-H
JP1: PINHD-1X16; 1X16
JP2: PINHD-1X3; 1X03
JP3: PINHD-1X4; 1X04
JP4, JP5, JP6: PINHD-1X2; 1X02
LED1: LED-5MM
R1: POTENTIOMETER; 3RP/1610N
R2, R3: 220; 1/4W-0.4
R4: 10k; 1/4W-0.4
U$1: ARDUINO_NANO

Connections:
5V: IC1.3 (OUT), JP1.2, JP2.1, JP3.4, R1.3 (E), R2.2, R4.2, U$1.VIN
24V: IC1.1 (IN), JP4.1
A: JP1.15, R2.1
BUTTON: JP6.1, R4.1, U$1.D8
D0: JP1.7
D1: JP1.8
D2: JP1.9
D3: JP1.10
D4: JP1.11, U$1.D4
D5: JP1.12, U$1.D5
D6: JP1.13, U$1.D6
D7: JP1.14, U$1.D7
EN: JP1.6, U$1.D3
GND: IC1.2 (GND), JP1.1, JP1.5, JP1.16, JP2.3, JP4.2, JP6.2, R1.1 (A), R3.1, U$1.GND
LED: LED1.A, U$1.D9
M_IN1: JP3.2, U$1.D11
M_IN2: JP3.3, U$1.D12
M_PWM: JP3.1, U$1.D10
unnamed: LED1.K (C), R3.2
POT: JP2.2, U$1.A0
RS: JP1.4, U$1.D2
RX: JP5.1, U$1.D0(RX)
TX: JP5.2, U$1.D1(TX)
VO: JP1.3, R1.2 (S)

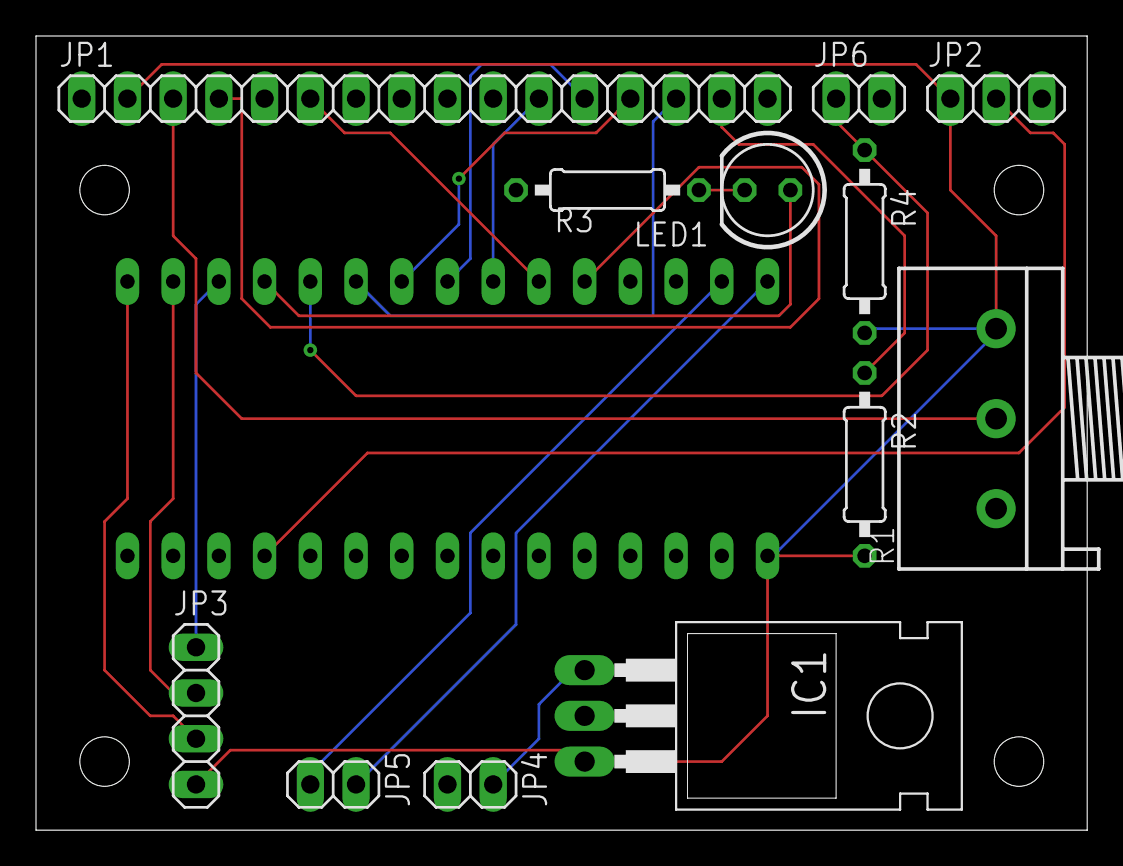
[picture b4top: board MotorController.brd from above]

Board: 2 copper layers, 58.4 x 44.1 mm, 13 parts (0 on the bottom side), 20 nets.
